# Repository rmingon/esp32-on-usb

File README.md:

# ESP32 USB STICK

Thank you to [PCBWay](https://www.pcbway.com/) for sponsorship the PCB production of this prototype.

## FIRST VIDEO

| GPIO  | LED |
| ------------- | ------------- |
| IO12  | D1  |
| IO13  | D2  |

### SOLDERED

### PCB BY PCBWAY

### 3D VIEW

### PCB VIEW

### SCHEMATIC VIEW

Thank you to [PCBWay](https://www.pcbway.com/) for sponsorship this project by covering the cost of PCB production for beta. The boards turned out very nicely. The black solder mask looks solid and the grills holes is perfect.

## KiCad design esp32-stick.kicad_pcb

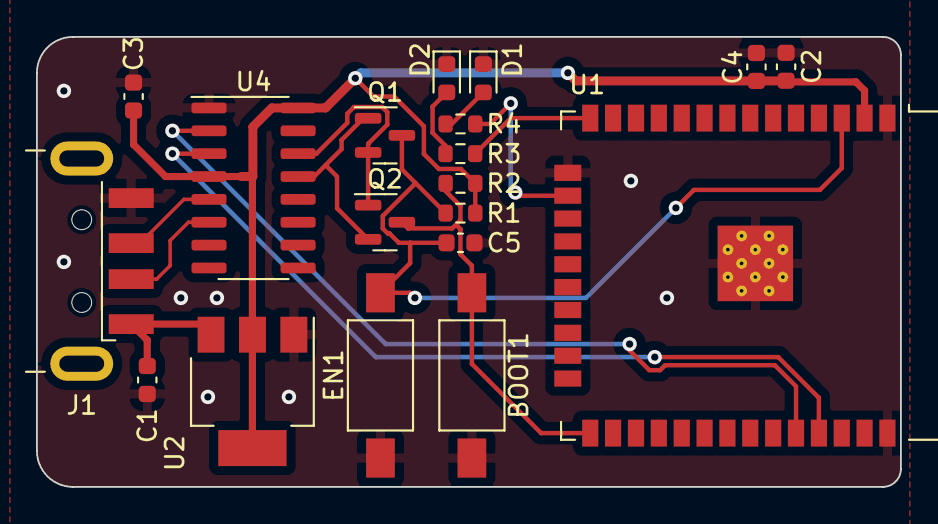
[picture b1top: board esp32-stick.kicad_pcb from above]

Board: 2 copper layers, 48.0 x 25.0 mm, 19 parts (0 on the bottom side), 15 nets.

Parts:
BOOT1: SW_Push; SW_SPST_FSMSM
C1, C2, C3, C4, C5: C; C_0603_1608Metric
D1, D2: LED; LED_0603_1608Metric
EN1: SW_Push; SW_SPST_FSMSM
J1: USB_A; USB_A_CNCTech_1001-011-01101_Horizontal
Q1, Q2: BSS138; SOT-23
R1, R2, R3, R4: R_Small; R_0603_1608Metric
U1: ESP32-WROOM-32
U2: AMS1117-3.3; SOT-223-3_TabPin2
U4: CH340C; SOIC-16_3.9x9.9mm_P1.27mm

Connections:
+3V3: C2.1, C3.1, C4.1, R1.1, R2.1, U1.2 (VDD), U2.2 (VO), U4.4 (V3), U4.16 (VCC)
+5V: C1.1, J1.1 (VBUS), U2.3 (VI)
D+: J1.3 (D+), U4.5 (UD+)
D-: J1.2 (D-), U4.6 (UD-)
ESP32_EN: C5.1, EN1.2, Q1.3 (D), R1.2, U1.3 (EN)
ESP32_IO0: BOOT1.1, Q2.3 (D), R2.2, U1.25 (IO0)
GND: BOOT1.2, C1.2, C2.2, C3.2, C4.2, C5.2, D1.1 (K), D2.1 (K), EN1.1, J1.4 (GND), U1.1 (GND), U1.15 (GND), U1.38 (GND), U1.39 (GND), U2.1 (GND), U4.1 (GND)
unnamed: D1.2 (A), R4.2
unnamed: D2.2 (A), R3.2
unnamed: Q1.1 (G), Q2.2 (S), U4.13 (~DTR)
unnamed: Q1.2 (S), Q2.1 (G), U4.14 (~RTS)
unnamed: R3.1, U1.14 (IO12)
unnamed: R4.1, U1.16 (IO13)
RX-PROG: U1.35 (TXD0/IO1), U4.3 (RXD)
TX-PROG: U1.34 (RXD0/IO3), U4.2 (TXD)

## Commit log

2024-06-24 add pcb
2024-06-24 board wiring
2024-06-24 wiring + fill zone
2024-06-24 add views
2024-06-24 Add README
2024-07-05 update sponsorship
2024-07-05 add pcbway views
2024-07-05 add soldered
2024-07-05 update with video
